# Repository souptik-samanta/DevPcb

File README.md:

# Infrared Gun 
A non-contact temperature meter made by [@souptik-samanta](https://github.com/souptik-samanta/)

---

## Features
- Custom 3D-printed **Case**
- Based on **STM32F103C8** microcontroller
- Breakout for many **GPIO pins**
- **USB-C** interface
- **RTC** (Real-Time Clock) capabilities
- Embedded microcontroller; low power consumption

### About the STM32F103C8
The **STMicroelectronics STM32F103C8** is an ARM Cortex-M3 32-bit microcontroller:
- 72MHz
- 64kB Flash, 20kB SRAM
- Internal 8MHz RC + 32kHz LSE
- RTC, Power saving modes
- JTAG + SWD debug
- 3 synchronous serial interfaces

---

## Why STM32 and not Arduino?
- More powerful and **cheaper**
- **Tough** and industrial-grade (like me )
- More GPIOs, fewer passives
- Doesn’t need a bloated dev board like the RP2040 or ATmega

### PCB Preview:

---

## Cost Breakdown

| Item                        | Cost (USD)  |
|-----------------------------|-------------|
| 5× PCBs (JLCPCB)            | $20         |
| Component parts             | $60         |
| Parts shipping              | $10         |
| Case shipping (Hack Club)  | $10         |
| **Total**                   | **~$100**    |

### EXPANDEDAdd commentMore actions
| Designator           | Footprint                                                       | Qty | Value              | LCSC Part # | Price ($) | Notes                      |
|----------------------|------------------------------------------------------------------|-----|---------------------|-------------|-----------|----------------------------|
| C1, C2, C3, C4       | 0402                                                             | 4   | 20pF               |             | 0.11      | Total: 49.55              |
| C10, C6, C7, C8, C9  | 0402                                                             | 5   | 100nF              |             | 0.32      | Shipping: $10             |
| C11                  | 0402                                                             | 1   | 1uF                |             | 0.24      | SO: $58, CSAE: $10        |
| C12, C13             | 0603                                                             | 2   | 22uF               |             | 3.63      | SO: $70                   |
| C5  | 0603                                                             | 1   | 100nF              |             | 0.25      | PCB Shipping: $20         |
|C|Charger"1"10ish $||
| D1, D2, D3           | 0603                                                             | 3   | LED                |             | 0.50      | SO: $100                   |
| FB1                  | 0603                                                             | 1   | FerriteBead_Small  |             | 0.70      | And misc costs            |
| J1                   | USB_C_Receptacle_GCT_USB4105-xx-A_16P_TopMnt_Horizontal         | 1   | USB_C_Receptacle   |             | 0.90      | Note: Price may increase  |
| J2                   | PinHeader_1x04_P2.54mm_Vertical                                 | 1   | MLX90614           |             | 15.00     |                            |
| J3                   | PinHeader_1x04_P2.54mm_Vertical                                 | 1   | OLED               |             | 3.00      |                            |
| OLED-Extra           | I2C Display Module                                               | 1   | OLED Display        |             | 2.00      |           |
| J5                   | PinSocket_2x10_P2.54mm_Vertical                                 | 1   | Conn_02x10         |             | 5.00      | Final Total: $98          |
| R1                   | 0402                                                             | 1   | 10K                |             | 0.30      |                            |
| R10, R11, R4         | 0402                                                             | 3   | 330                |             | 0.50      |                            |
| R3                   | 0402                                                             | 1   | 0                  |             | 1.00      |                            |
| R5, R6               | 0402                                                             | 2   | 20R                |             | 0.50      |                            |
| R7                   | 0402                                                             | 1   | 1.5K               |             | 0.70      |                            |
| R8, R9               | 0402                                                             | 2   | 5.1K               |             | 0.90      |                            |
| SW1                  | SW_TS-1088-AR02016                                               | 1   | BOOTSEL            |             | 1.00      |                            |
| SW2                  | SW_TS-1088-AR02016                                               | 1   | RST                |             | 1.00      |                            |
| U1                   | LQFP-48_7x7mm_P0.5mm                                             | 1   | STM32F103C8Tx      |             | 8.00      |                            |
| U2                   | SOT-223-3_TabPin2                                                | 1   | AMS1117-3.3        |             | 1.00      |                            |
| U3                   | SOT-23-6_Handsoldering                                           | 1   | SRV05-4            |             | 1.00      |                            |
| Y1                   | Crystal_SMD_3225-4Pin_3.2x2.5mm                                  | 1   | 8MHz               |             | 0.80      |                            |
| Y3                   | Crystal_SMD_3215-2Pin_3.2x1.5mm                                  | 1   | 32.768            |             | 1.20      |                            |
battries from burger 5$$
###

[Full BOM (Google Sheets)](https://docs.google.com/spreadsheets/d/1CJmj2ZeR5zD6k4xkK5MPgWyc9Sze1-qekb7O28ZE8Ps/edit?usp=sharing)

---

## 🎞️ Disintregreted View Animation(Wait for sometime)

## JLCPCB RENDER

###

.png>)

###

###

###

###

###

###

###
---

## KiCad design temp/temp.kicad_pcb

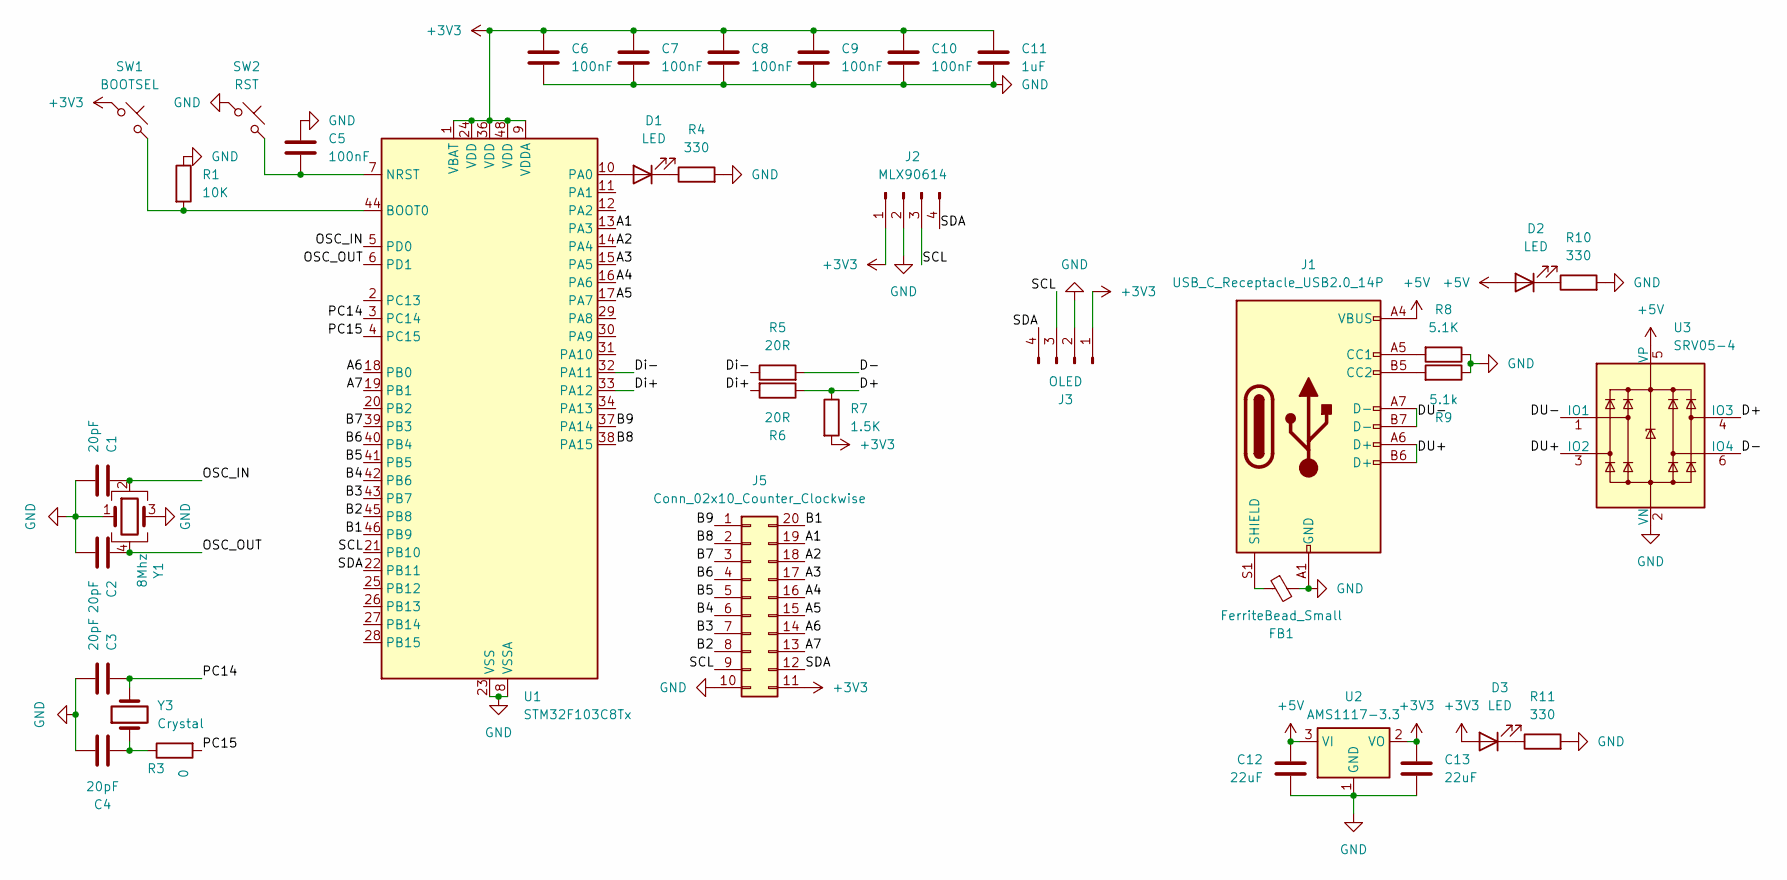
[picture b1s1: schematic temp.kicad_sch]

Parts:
C1, C2, C3, C4: 20pF; C_0402_1005Metric
C5: 100nF; C_0603_1608Metric
C6, C7, C8, C9, C10: 100nF; C_0402_1005Metric
C11: 1uF; C_0402_1005Metric
C12, C13: 22uF; C_0603_1608Metric
D1, D2, D3: LED; LED_0603_1608Metric
FB1: FerriteBead_Small; L_0603_1608Metric_Pad1.05x0.95mm_HandSolder
J1: USB_C_Receptacle_USB2.0_14P; USB_C_Receptacle_GCT_USB4105-xx-A_16P_TopMnt_Horizontal
J2: MLX90614; PinHeader_1x04_P2.54mm_Vertical
J3: OLED; PinHeader_1x04_P2.54mm_Vertical
J5: Conn_02x10_Counter_Clockwise; PinSocket_2x10_P2.54mm_Vertical
R1: 10K; R_0402_1005Metric
R3: 0; R_0402_1005Metric
R4, R10, R11: 330; R_0402_1005Metric
R5, R6: 20R; R_0402_1005Metric
R7: 1.5K; R_0402_1005Metric
R8: 5.1K; R_0402_1005Metric
R9: 5.1k; R_0402_1005Metric
SW1: BOOTSEL; SW_TS-1088-AR02016
SW2: RST; SW_TS-1088-AR02016
U1: STM32F103C8Tx; LQFP-48_7x7mm_P0.5mm
U2: AMS1117-3.3; SOT-223-3_TabPin2
U3: SRV05-4; SOT-23-6_Handsoldering
Y1: 8Mhz; Crystal_SMD_3225-4Pin_3.2x2.5mm
Y3: Crystal; Crystal_SMD_3215-2Pin_3.2x1.5mm

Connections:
+3V3: C6.1, C7.1, C8.1, C9.1, C10.1, C11.1, C13.1, D3.2 (A), J2.1, J3.1, J5.11, R7.2, SW1.1, U1.1 (VBAT), U1.9 (VDDA), U1.24 (VDD), U1.36 (VDD), U1.48 (VDD), U2.2 (VO)
+5V: C12.1, D2.2 (A), J1.A4 (VBUS), J1.A9 (VBUS), J1.B4 (VBUS), J1.B9 (VBUS), U2.3 (VI), U3.5 (VP)
/A1: J5.19, U1.13 (PA3)
/A2: J5.18, U1.14 (PA4)
/A3: J5.17, U1.15 (PA5)
/A4: J5.16, U1.16 (PA6)
/A5: J5.15, U1.17 (PA7)
/A6: J5.14, U1.18 (PB0)
/A7: J5.13, U1.19 (PB1)
/B1: J5.20, U1.46 (PB9)
/B2: J5.8, U1.45 (PB8)
/B3: J5.7, U1.43 (PB7)
/B4: J5.6, U1.42 (PB6)
/B5: J5.5, U1.41 (PB5)
/B6: J5.4, U1.40 (PB4)
/B7: J5.3, U1.39 (PB3)
/B8: J5.2, U1.38 (PA15)
/B9: J5.1, U1.37 (PA14)
/D+: R6.1, R7.1, U3.4 (IO3)
/D-: R5.2, U3.6 (IO4)
/DU+: J1.A6 (D+), J1.B6 (D+), U3.3 (IO2)
/DU-: J1.A7 (D-), J1.B7 (D-), U3.1 (IO1)
/Di+: R6.2, U1.33 (PA12)
/Di-: R5.1, U1.32 (PA11)
/OSC_IN: C1.1, U1.5 (PD0), Y1.2
/OSC_OUT: C2.1, U1.6 (PD1), Y1.4
/PC14: C3.1, U1.3 (PC14), Y3.2
/PC15: R3.2, U1.4 (PC15)
/SCL: J2.3, J3.3, J5.9, U1.21 (PB10)
/SDA: J2.4, J3.4, J5.12, U1.22 (PB11)
GND: C1.2, C2.2, C3.2, C4.1, C5.1, C6.2, C7.2, C8.2, C9.2, C10.2, C11.2, C12.2, C13.2, FB1.2, J1.A1 (GND), J1.A12 (GND), J1.B1 (GND), J1.B12 (GND), J2.2, J3.2, J5.10, R1.1, R4.2, R8.1, R9.1, R10.2, R11.2, SW2.1, U1.8 (VSSA), U1.23 (VSS), U1.35 (VSS), U1.47 (VSS), U2.1 (GND), U3.2 (VN), Y1.1, Y1.3
unnamed: C4.2, R3.1, Y3.1
unnamed: D1.2 (A), U1.10 (PA0)
unnamed: D1.1 (K), R4.1
unnamed: D2.1 (K), R10.1
unnamed: D3.1 (K), R11.1
unnamed: J1.A5 (CC1), R8.2
unnamed: J1.B5 (CC2), R9.2
unnamed: FB1.1, J1.S1 (SHIELD)
unnamed: R1.2, SW1.2, U1.44 (BOOT0)
unnamed: C5.2, SW2.2, U1.7 (NRST)

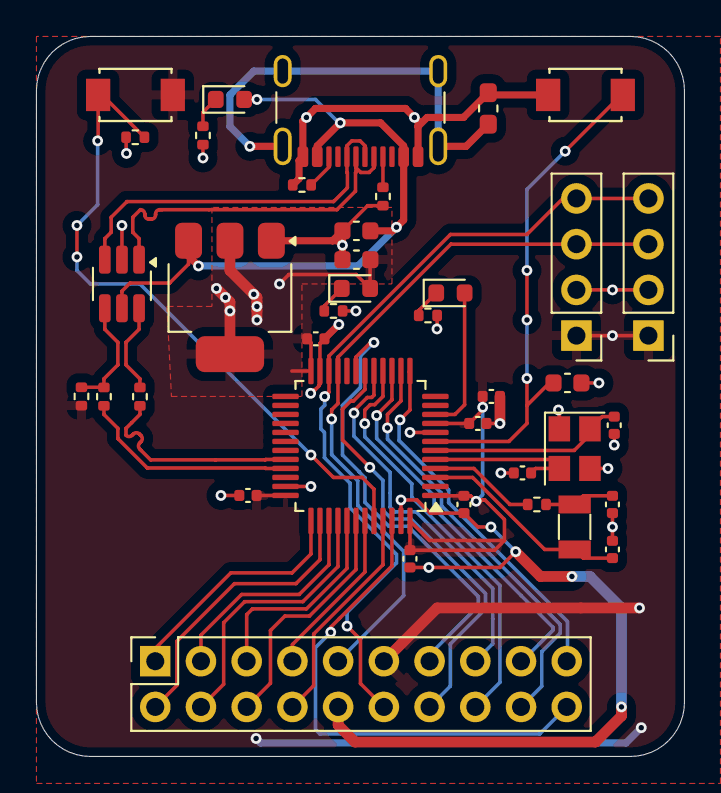
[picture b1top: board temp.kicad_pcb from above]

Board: 2 copper layers, 36.0 x 40.0 mm, 38 parts (0 on the bottom side), 41 nets.

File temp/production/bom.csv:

Designator,Footprint,Quantity,Value,LCSC Part #
"C1, C2, C3, C4",0402,4,20pF,
"C10, C6, C7, C8, C9",0402,5,100nF,
C11,0402,1,1uF,
"C12, C13",0603,2,22uF,
C5,0603,1,100nF,
"D1, D2, D3",0603,3,LED,
FB1,0603,1,FerriteBead_Small,
J1,USB_C_Receptacle_GCT_USB4105-xx-A_16P_TopMnt_Horizontal,1,USB_C_Receptacle_USB2.0_14P,
J2,PinHeader_1x04_P2.54mm_Vertical,1,MLX90614,
J3,PinHeader_1x04_P2.54mm_Vertical,1,OLED,
J5,PinSocket_2x10_P2.54mm_Vertical,1,Conn_02x10_Counter_Clockwise,
R1,0402,1,10K,
"R10, R11, R4",0402,3,330,
R3,0402,1,0,
"R5, R6",0402,2,20R,
R7,0402,1,1.5K,
"R8, R9",0402,2,5.1K,
SW1,SW_TS-1088-AR02016,1,BOOTSEL,
SW2,SW_TS-1088-AR02016,1,RST,
U1,LQFP-48_7x7mm_P0.5mm,1,STM32F103C8Tx,
U2,SOT-223-3_TabPin2,1,AMS1117-3.3,
U3,SOT-23-6_Handsoldering,1,SRV05-4,
Y1,Crystal_SMD_3225-4Pin_3.2x2.5mm,1,8Mhz,
Y3,Crystal_SMD_3215-2Pin_3.2x1.5mm,1,Crystal,

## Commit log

2025-06-15 day 1
2025-06-15 day 2
2025-06-22 day 4
2025-06-22 pcb fully done now time for case
2025-06-23 final ig?
2025-06-23 readme
2025-06-23 fix bold
2025-06-23 fix readme
2025-06-23 FINALL FKING DONE
2025-06-23 DONEEEE
2025-06-23 fogot the firmare:
2025-06-23 rm asd
2025-06-23 3d parts added
2025-06-23 onemore
2025-06-24 formating
